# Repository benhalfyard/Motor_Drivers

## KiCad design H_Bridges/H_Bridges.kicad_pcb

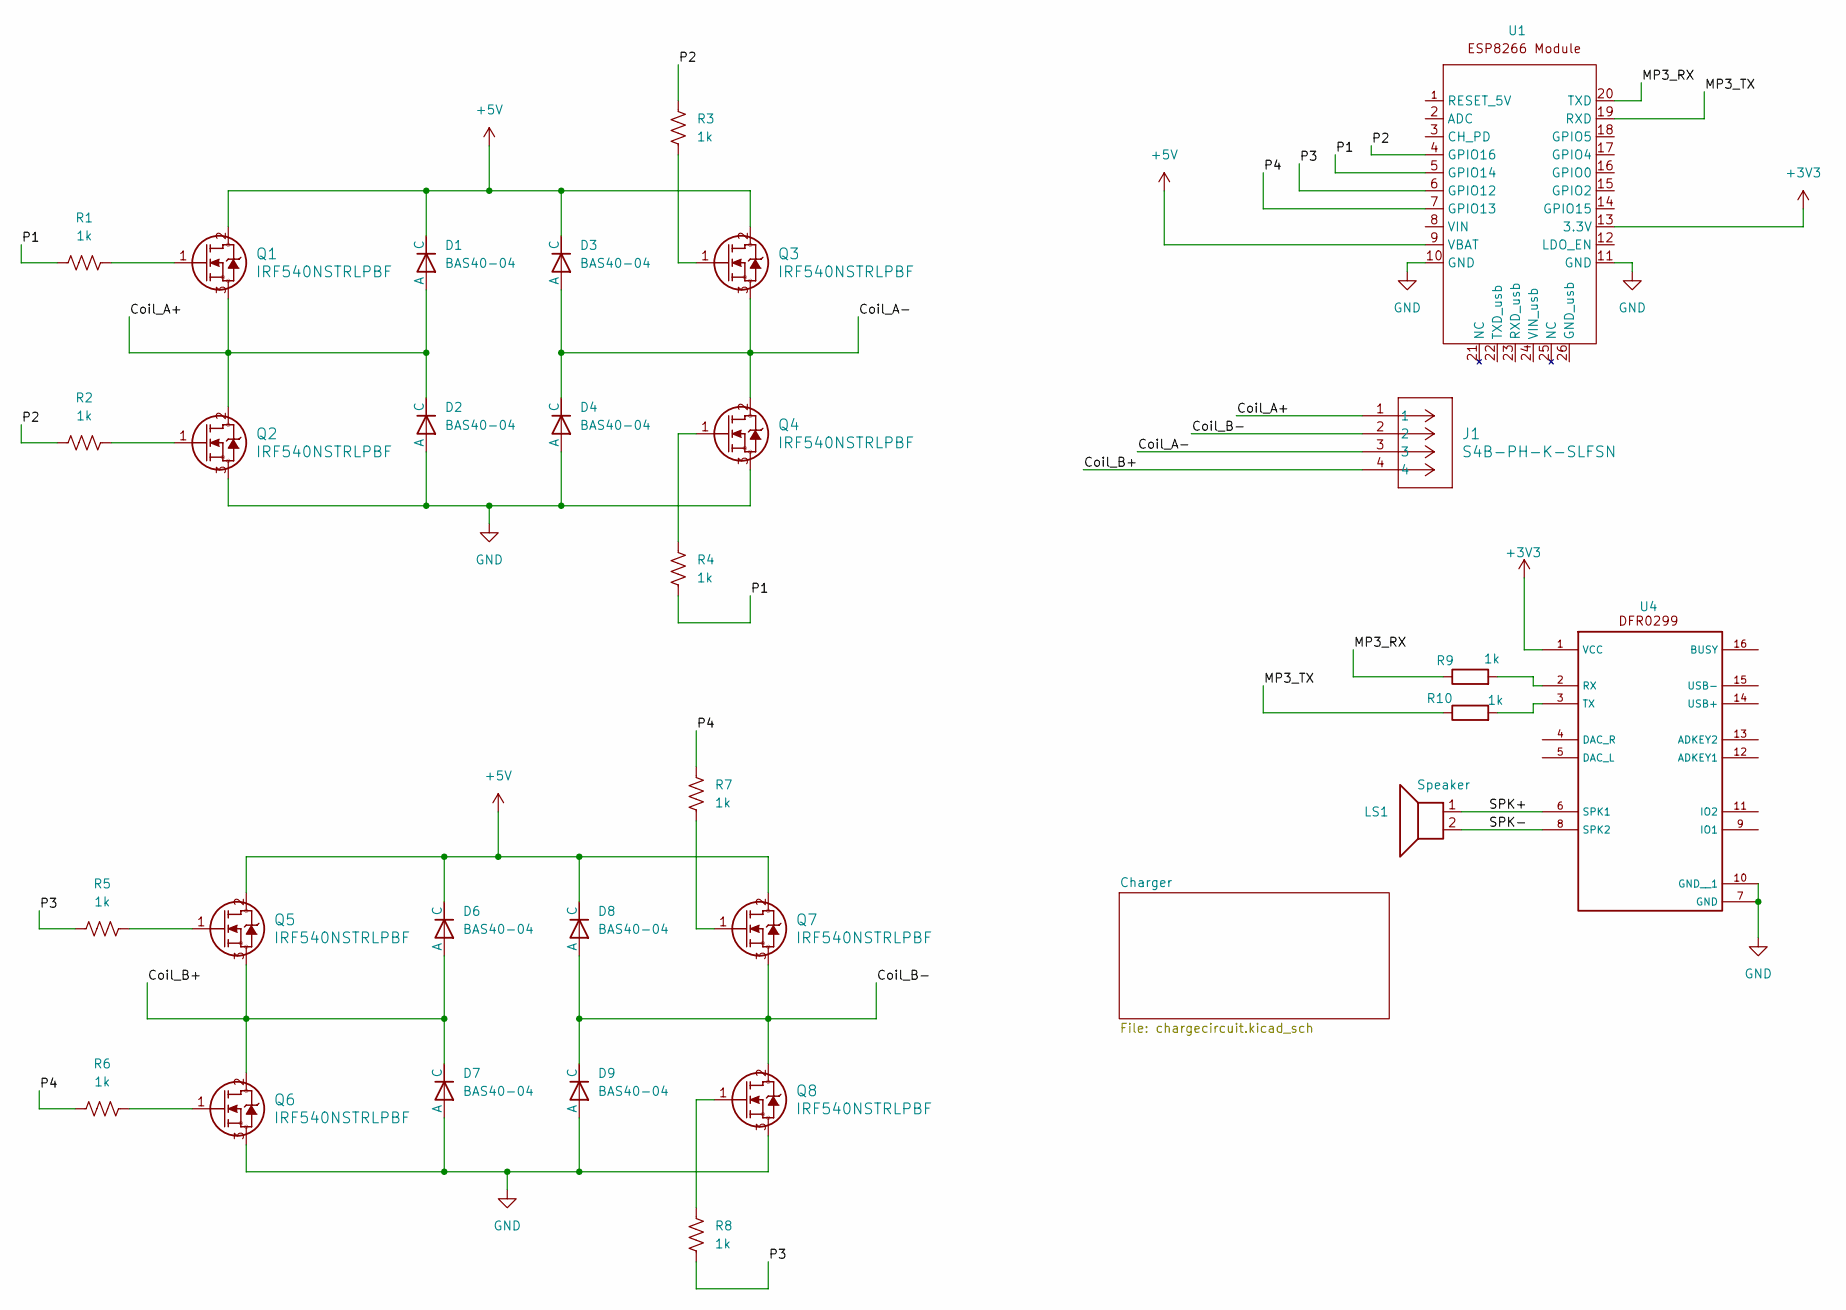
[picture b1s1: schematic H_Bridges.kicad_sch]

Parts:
D1, D2, D3, D4, D6, D7, D8, D9: BAS40-04; P200_SOT-23
J1: S4B-PH-K-SLFSN; CONN_S4B-PH-K-S_JST
LS1: Speaker
Q1, Q2, Q3, Q4, Q5, Q6, Q7, Q8: IRF540NSTRLPBF; D2PAK
R1, R2, R3, R4, R5, R6, R7, R8: 1k; R_0603_1608Metric
R9, R10: 1k; R_0402_1005Metric
U1: ESP8266; Adafruit_HUZZAH_ESP8266_breakout
U4: MODULE_DFR0299

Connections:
+3V3: U1.13 (3.3V), U4.1 (VCC)
+5V: D1.2 (C), D3.2 (C), D6.2 (C), D8.2 (C), Q1.2, Q3.2, Q5.2, Q7.2, U1.9 (VBAT); also elsewhere on the board
/Coil_A+: D1.1 (A), D2.2 (C), J1.1, Q1.3, Q2.2
/Coil_A-: D3.1 (A), D4.2 (C), J1.3, Q3.3, Q4.2
/Coil_B+: D6.1 (A), D7.2 (C), J1.4, Q5.3, Q6.2
/Coil_B-: D8.1 (A), D9.2 (C), J1.2, Q7.3, Q8.2
/MP3_RX: R9.1, U1.20 (TXD)
/MP3_TX: R10.1, U1.19 (RXD)
/P1: R1.1, R4.1, U1.5 (GPIO14)
/P2: R2.1, R3.2, U1.4 (GPIO16)
/P3: R5.1, R8.1, U1.6 (GPIO12)
/P4: R6.1, R7.2, U1.7 (GPIO13)
/SPK+: LS1.1, U4.6 (SPK1)
/SPK-: LS1.2, U4.8 (SPK2)
GND: D2.1 (A), D4.1 (A), D7.1 (A), D9.1 (A), Q2.3, Q4.3, Q6.3, Q8.3, U1.10 (GND), U1.11 (GND), U4.7 (GND), U4.10 (GND__1); also elsewhere on the board
unnamed: Q1.1, R1.2
unnamed: Q2.1, R2.2
unnamed: Q3.1, R3.1
unnamed: Q4.1, R4.2
unnamed: Q5.1, R5.2
unnamed: Q6.1, R6.2
unnamed: Q7.1, R7.1
unnamed: Q8.1, R8.2
unnamed: R9.2, U4.2 (RX)
unnamed: R10.2, U4.3 (TX)

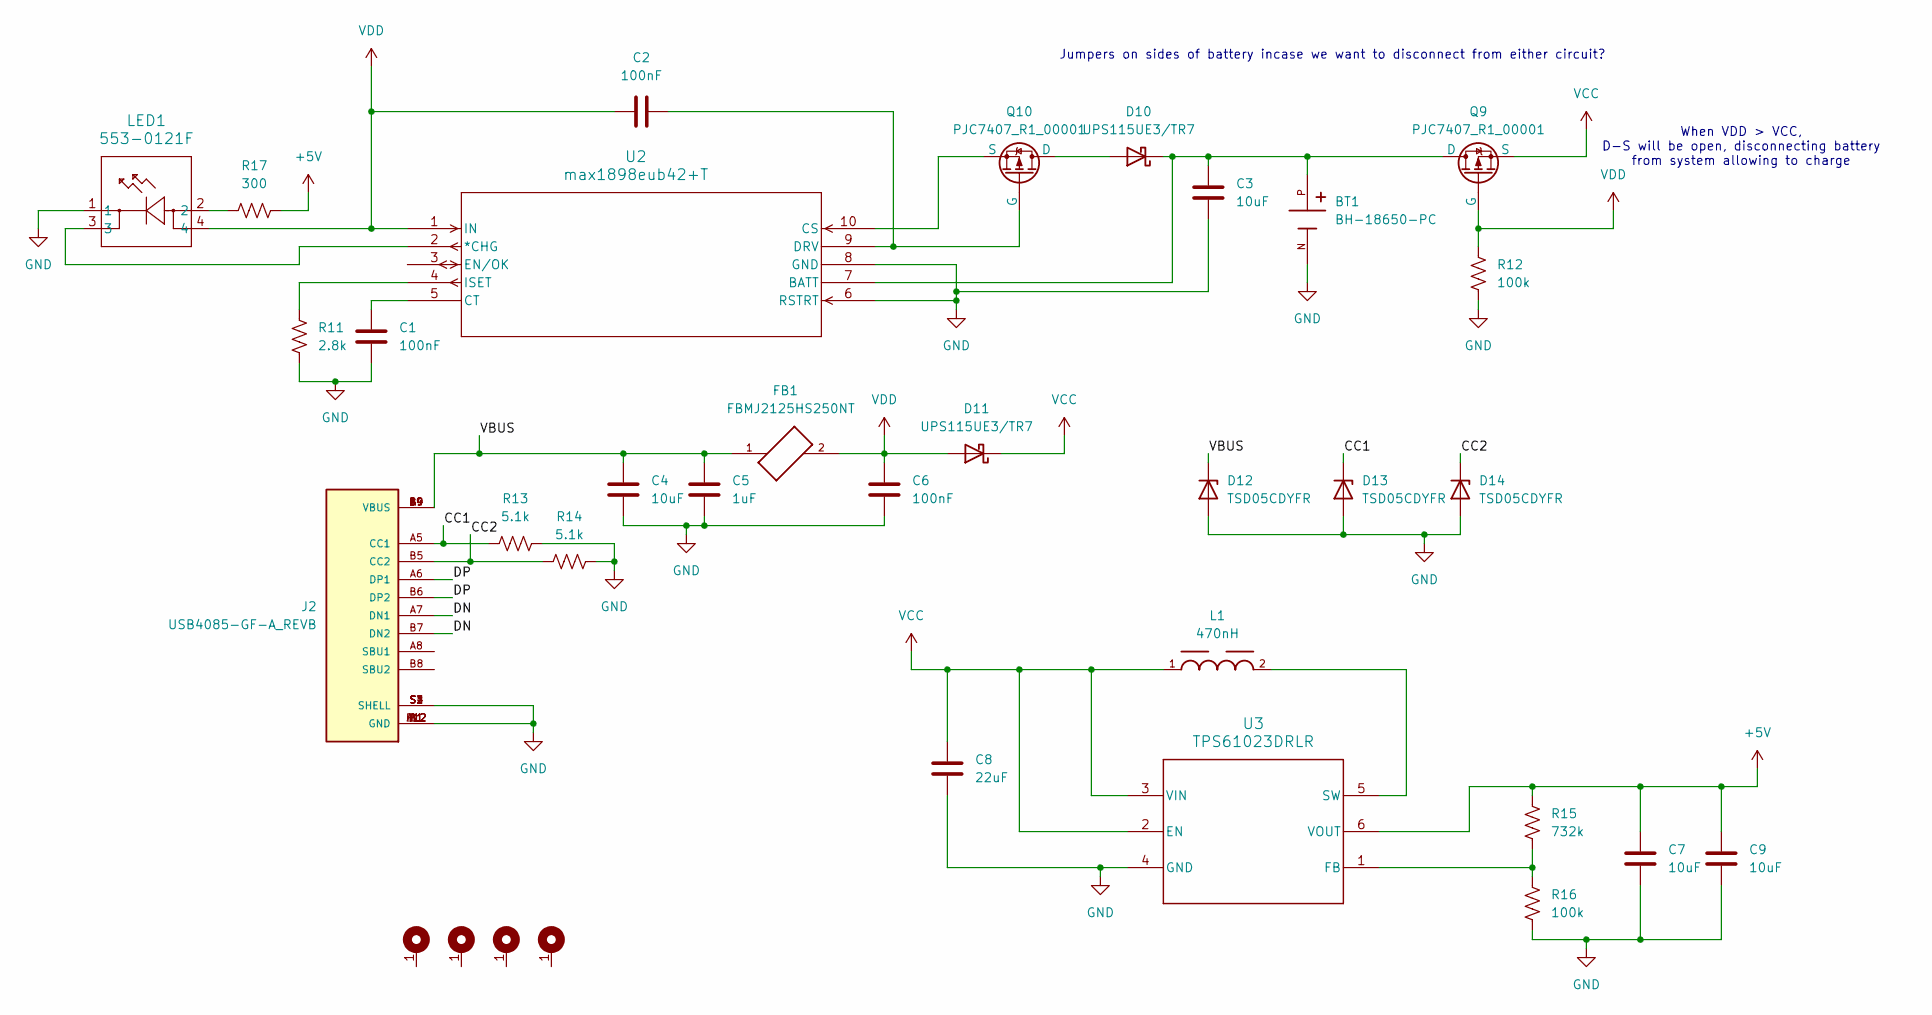
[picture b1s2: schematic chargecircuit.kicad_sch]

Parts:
BT1: BH-18650-PC; BAT_BH-18650-PC; PARTREV 05/17/19
C1, C2, C6: 100nF; C_0603_1608Metric
C3, C4, C7, C9: 10uF; C_0603_1608Metric
C5: 1uF; C_0603_1608Metric
C8: 22uF; C_0603_1608Metric
D10, D11: UPS115UE3/TR7; POWERMITE1_DO-216AA_MIS_MCH
D12, D13, D14: TSD05CDYFR; TVS_SOD2_DYF_TEX-L
FB1: FBMJ2125HS250NT; BEADC2012X105N
H1, H2, H3, H4: MountingHole; MountingHole_3mm_Pad_TopBottom
J2: USB4085-GF-A_REVB; GCT_USB4085-GF-A_REVB; PARTREV B; DigiKey_Part_Number 2073-USB4085-GF-ATR-ND
L1: 470nH; WE-MAPI_3015
LED1: 553-0121F; 553-0121F_DIA
Q9, Q10: PJC7407_R1_00001; SOT65P210X110-3N
R11: 2.8k; R_0603_1608Metric
R12, R16: 100k; R_0603_1608Metric
R13, R14: 5.1k; R_0603_1608Metric
R15: 732k; R_0603_1608Metric
R17: 300; R_0603_1608Metric
U2: max1898eub42+T; 21-0061L_MXM
U3: TPS61023DRLR; DRL0006A

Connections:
+5V: C7.1, C9.1, R15.1, R17.2, U3.6 (VOUT); also elsewhere on the board
/Charger/CC1: D13.1 (K), J2.A5 (CC1), R13.1
/Charger/CC2: D14.1 (K), J2.B5 (CC2), R14.1
/Charger/DN: J2.A7 (DN1), J2.B7 (DN2)
/Charger/DP: J2.A6 (DP1), J2.B6 (DP2)
/Charger/VBUS: C4.1, C5.1, D12.1 (K), FB1.1, J2.A4 (VBUS), J2.A9 (VBUS), J2.B4 (VBUS), J2.B9 (VBUS)
GND: BT1.N, C1.2, C3.2, C4.2, C5.2, C6.2, C7.2, C8.2, C9.2, D12.2 (A), D13.2 (A), D14.2 (A), J2.A1 (GND), J2.A12 (GND), J2.B1 (GND), J2.B12 (GND), J2.S1 (SHELL), J2.S2 (SHELL), J2.S3 (SHELL), J2.S4 (SHELL), LED1.1, R11.2, R12.2, R13.2, R14.2, R16.2, U2.6 (RSTRT), U2.8 (GND), U3.4 (GND); also elsewhere on the board
unnamed: D10.2 (A), Q10.1 (D)
unnamed: BT1.P, C3.1, D10.1 (K), Q9.1 (D), U2.7 (BATT)
unnamed: LED1.2, R17.1
unnamed: C2.2, Q10.2 (G), U2.9 (DRV)
unnamed: Q10.3 (S), U2.10 (CS)
unnamed: LED1.3, U2.2 (*CHG)
unnamed: C1.1, U2.5 (CT)
unnamed: R11.1, U2.4 (ISET)
unnamed: R15.2, R16.1, U3.1 (FB)
unnamed: L1.2, U3.5 (SW)
VCC: C8.1, D11.1 (K), L1.1, Q9.3 (S), U3.2 (EN), U3.3 (VIN)
VDD: C2.1, C6.1, D11.2 (A), FB1.2, LED1.4, Q9.2 (G), R12.1, U2.1 (IN)

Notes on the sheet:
Jumpers on sides of battery incase we want to disconnect from either circuit?
When VDD > VCC, D-S will be open, disconnecting battery from system allowing to charge

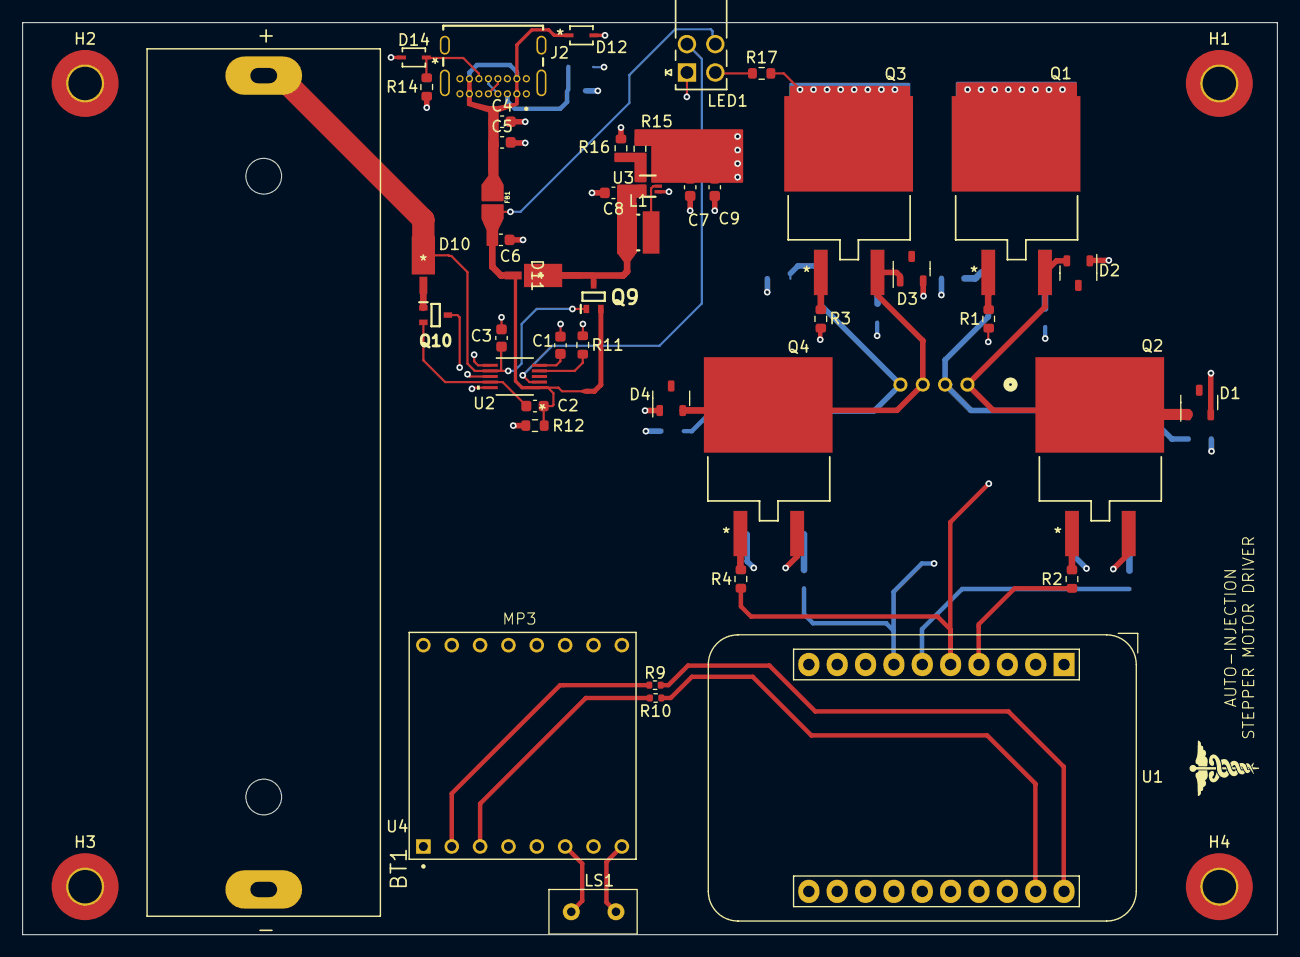
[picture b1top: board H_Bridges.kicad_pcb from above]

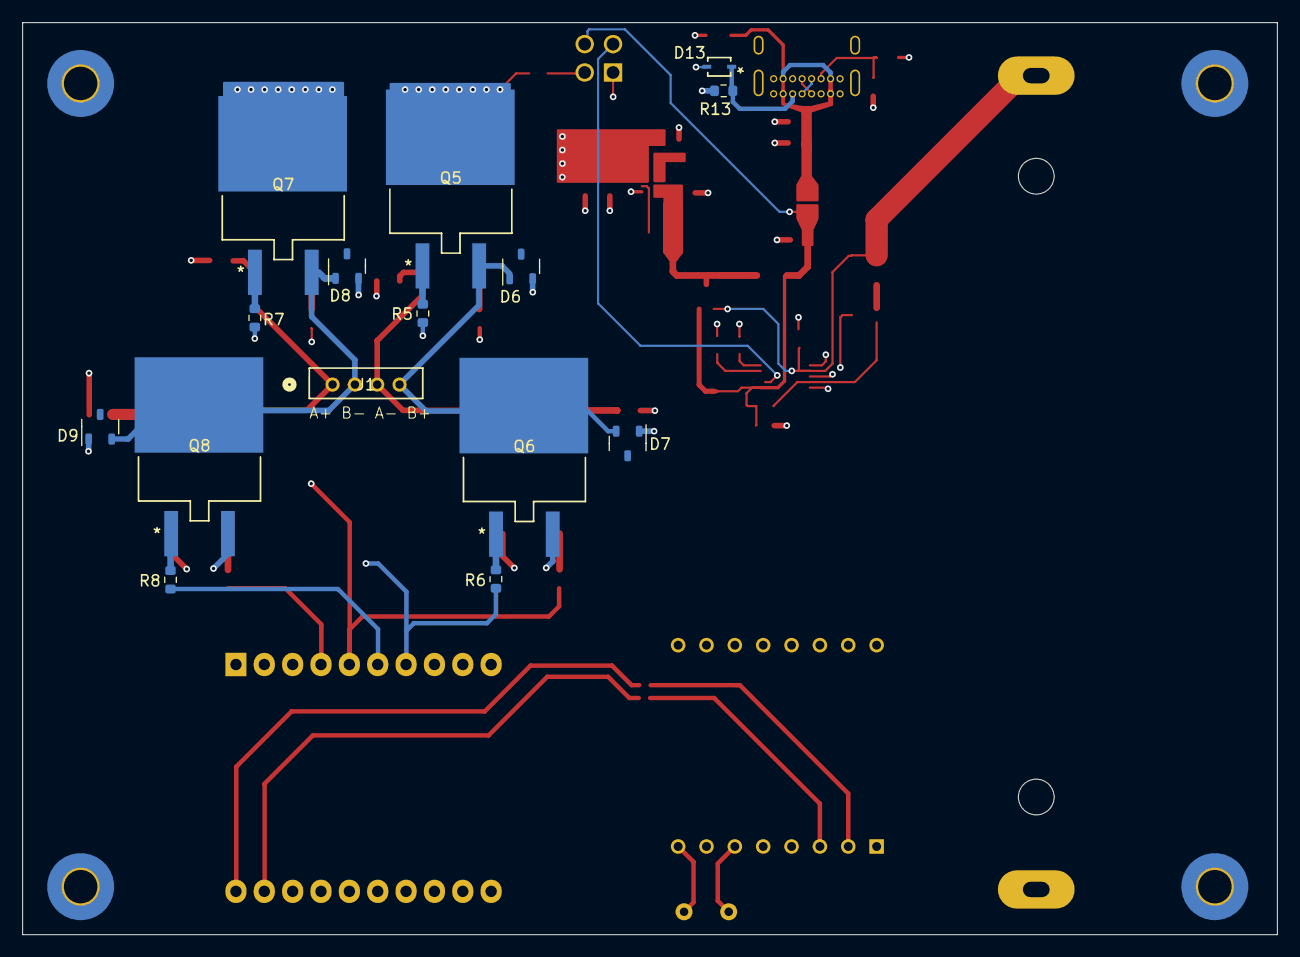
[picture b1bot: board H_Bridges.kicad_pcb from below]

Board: 4 copper layers, 112.4 x 81.7 mm, 64 parts (15 on the bottom side), 42 nets.

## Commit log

2025-01-17 H-Bridge Schematics
2025-01-21 added connector
2025-01-22 created footprint for ESP
2025-01-24 added 0 ohms
2025-01-25 added battery + sym/foot
2025-01-26 started charge circuit
2025-01-27 designed charge circuit
2025-01-28 USB-C Input and Isolation Circuit
2025-01-29 designed boost converter
2025-01-29 changed boost regulator
2025-01-29 added resistor footprints
2025-01-30 exported Layout
2025-01-31 started placement
2025-02-03 finished component placement
2025-02-03 placement fixes
2025-02-04 routing start
2025-02-04 power routing
2025-02-05 finished routing
2025-02-06 added sim for H-bridge
2025-02-06 updated inductor footprint
2025-02-07 made final changes
2025-02-07 Fab Outputs
2025-02-07 RE-FAB
